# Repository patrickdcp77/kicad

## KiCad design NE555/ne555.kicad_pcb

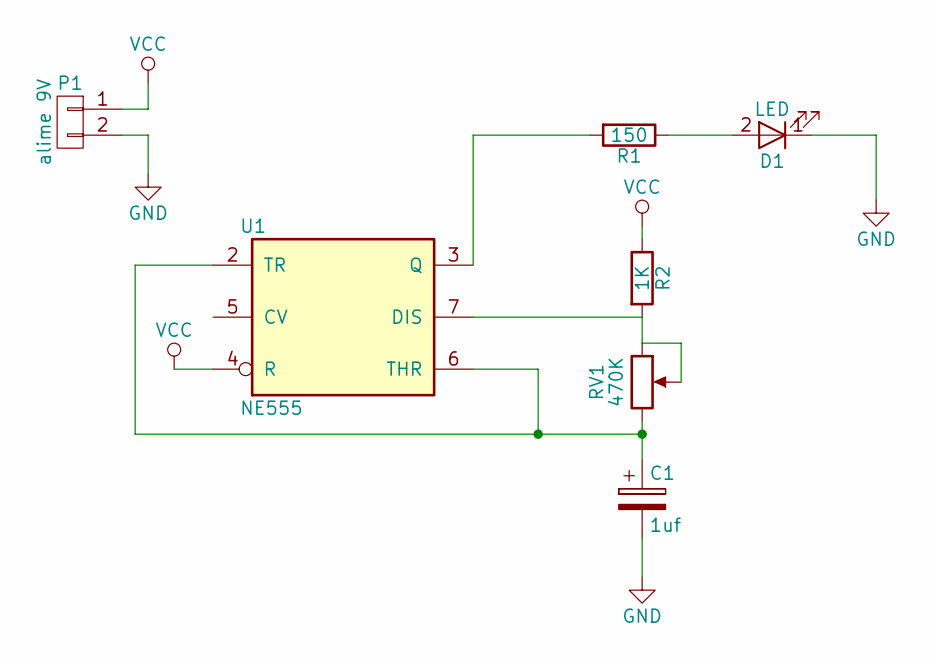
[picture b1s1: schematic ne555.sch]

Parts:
C1: 1uf; CP_Radial_D5.0mm_P2.50mm
D1: LED; LED_D3.0mm
P1: alime 9V; Socket_Strip_Straight_1x02_Pitch2.54mm
R1: 150; R_Axial_DIN0207_L6.3mm_D2.5mm_P7.62mm_Horizontal
R2: 1K; R_Axial_DIN0207_L6.3mm_D2.5mm_P7.62mm_Horizontal
RV1: 470K; Socket_Strip_Straight_1x03_Pitch2.54mm
U1: NE555; DIP-8_W7.62mm

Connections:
GND: C1.2, D1.1 (K), P1.2, U1.1 (GND)
unnamed: C1.1, RV1.3, U1.2 (TR), U1.6 (THR)
unnamed: D1.2 (A), R1.1
unnamed: R1.2, U1.3 (Q)
unnamed: R2.2, RV1.1, RV1.2, U1.7 (DIS)
VCC: P1.1, R2.1, U1.4 (R), U1.8 (VCC)

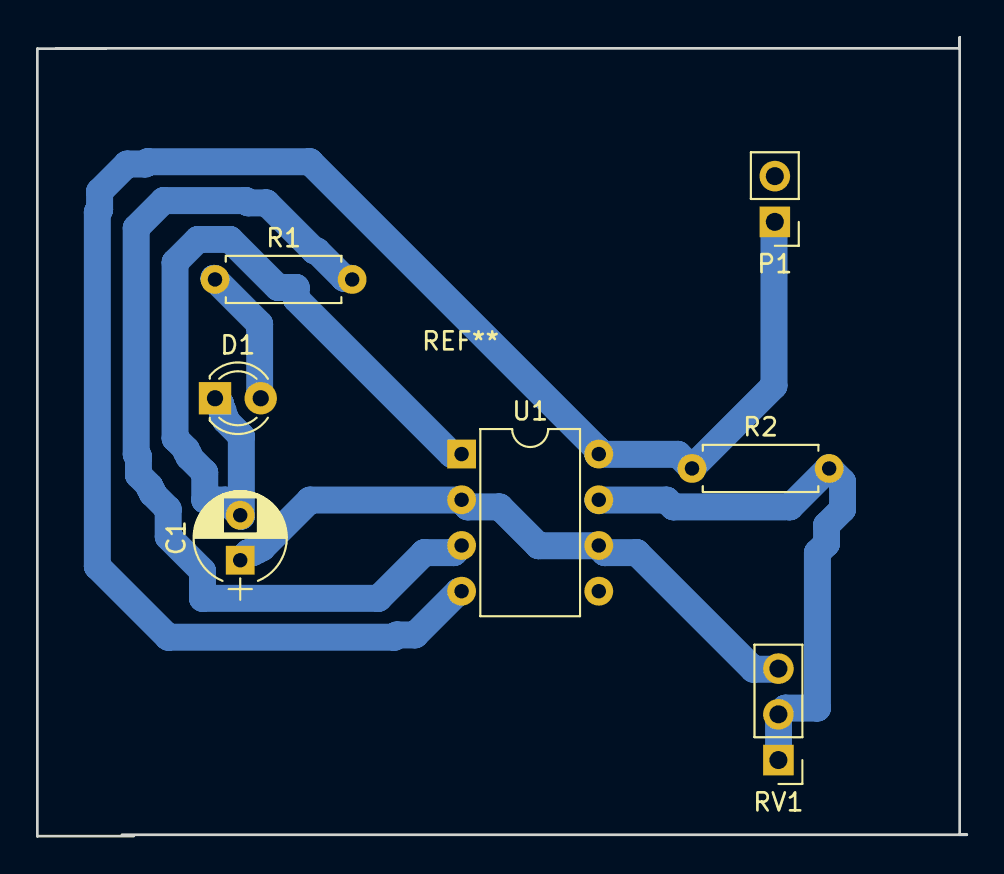
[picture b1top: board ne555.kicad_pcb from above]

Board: 2 copper layers, 51.6 x 44.4 mm, 7 parts (0 on the bottom side), 6 nets.

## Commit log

2017-03-30 1ere validation
